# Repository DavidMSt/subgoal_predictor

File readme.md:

# subgoal predictor

Software accompanying the Master's thesis:

**Consensus through Learning: Graph Neural Networks for Task Allocation under Motion Constraints**

This repository contains the simulation and learning code developed for the thesis. It builds on the BilboLab robotics framework originally developed at the Control Systems Group, TU Berlin, and extends it with thesis-specific modules for multi-agent task assignment, motion planning, trajectory execution, and reinforcement-learning-based subgoal prediction.

The thesis investigates whether a learned coordination layer can improve multi-robot task execution in spatially constrained environments. The focus is not end-to-end learned control. Instead, the learned policy predicts intermediate subgoals and wait times, while trajectory generation remains handled by a classical motion-planning pipeline.

---

## Repository status

This repository contains research code produced for a Master's thesis. It is not a cleaned production framework.

The repository state corresponding to the thesis submission is tagged as:

```text
thesis-submission-2026-04-30
```

Use this tag, or the exact commit hash referenced in the thesis, when reproducing results.

The most relevant thesis-specific code is located in:

```text
software/master_thesis/
```

The rest of the repository contains the underlying BilboLab framework, robot infrastructure, GUI components, simulation utilities, firmware-related files, and hardware/testbed material inherited from or derived from the upstream BilboLab project.

---

## Thesis-specific contribution

The thesis-specific implementation extends BilboLab with a modular multi-agent coordination pipeline:

```text
Task Assignment → Subgoal Prediction → Motion Planning → Execution
```

The main components are:

- **Task assignment module**  
  Provides interfaces for assigning agents to tasks. Classical strategies such as the Hungarian algorithm are used for evaluation. DGNN-GA-related code is included as a compatible decentralized assignment component, but the final thesis evaluation fixes assignment with the Hungarian algorithm in order to isolate the subgoal predictor.

- **Subgoal predictor**  
  Reinforcement-learning policy trained to predict intermediate positions and wait times. The goal is to stage agents before contested passages and reduce unresolved congestion.

- **Motion-planning module**  
  OMPL/FCL-based planning pipeline for generating collision-checked paths under the robot model. Planned paths are post-processed and converted into executable trajectories.

- **Execution module**  
  Applies planned trajectories step by step in the BilboLab simulation loop and handles waiting phases, task completion, and replanning/failure states.

- **Scenario and evaluation infrastructure**  
  Contains fixed and randomized multi-agent scenarios used for training, evaluation, debugging, and visualization.

---

## Directory overview

The thesis-specific package is structured as follows:

```text
software/master_thesis/
├── containers/          # Shared state/config containers
├── general/             # Base thesis-specific simulation and agent layer
├── universal/           # Extended simulation/agent layer with TA → MP → EXE pipeline
├── modules/
│   ├── task_assignment/     # Assignment interfaces and solvers
│   ├── motion_planning/     # OMPL/FCL planning and trajectory generation
│   ├── execution/           # Trajectory execution and reactive execution logic
│   ├── subgoal_predictor/   # RL subgoal policy, training, inference, and design notes
│   └── local_control/       # Low-level/local controller experiments
├── scenarios/           # Scenario definitions and YAML files
└── gui/                 # Thesis-specific GUI entry points
```

The top-level repository also contains the broader BilboLab structure:

```text
software/       # Host-side framework and thesis code
robots/         # Robot platform code and related infrastructure
libraries/      # Shared software libraries
testbed/        # Physical testbed configuration
electronics/    # Electronics-related material
material/        # Supporting material
```

---

## Main thesis pipeline

The evaluated pipeline fixes task assignment using the Hungarian algorithm in order to isolate the learned subgoal predictor. The learned policy is then evaluated as an intermediate coordination layer between task assignment and motion planning.

The execution flow is:

1. Load a multi-agent scenario.
2. Assign each agent to one task.
3. Construct local observations for each agent.
4. Predict optional subgoals and wait times.
5. Plan motion to subgoals and final tasks.
6. Execute planned trajectories in simulation.
7. Log termination rate, makespan, planning failures, planning time, wait time, and subgoal-related metrics.

This separation is important: the policy does not replace the motion planner. It only changes the intermediate targets given to the planner.

---

## Important modules

### Task assignment

```text
software/master_thesis/modules/task_assignment/
```

Contains the task-assignment interface and available assignment strategies. The final experiments use the Hungarian algorithm as a fixed assignment solver to isolate the subgoal predictor. DGNN-GA-related code is included as a decentralized assignment option and system-level compatibility component, but the final thesis results do not evaluate the full DGNN-GA + subgoal-prediction pipeline.

### Motion planning

```text
software/master_thesis/modules/motion_planning/
```

Contains the planner interface, OMPL adapter, trajectory planner, and related planning utilities. The planner receives agent state, target state, map information, and robot geometry, then returns either a trajectory representation or a planning failure state.

### Execution

```text
software/master_thesis/modules/execution/
```

Contains the logic that applies planned trajectories during the simulation loop. This layer bridges planner output and simulated robot motion.

### Subgoal prediction

```text
software/master_thesis/modules/subgoal_predictor/
```

Contains the reinforcement-learning subgoal predictor, training code, subgoal manager, and design notes. The policy predicts intermediate target positions and wait times from local observations. These predictions are passed back into the same motion-planning and execution modules used by the non-learning baseline.

Relevant files include:

```text
rl_subgoal_predictor.py
subgoal_manager.py
train_subgoal.py
architecture_notes.md
obs_design_notes.md
reward_design_notes.md
```

### Scenarios

```text
software/master_thesis/scenarios/
```

Contains YAML and Python scenario definitions. The scenarios include fixed and randomized setups with different numbers of agents and bottleneck configurations, such as one-gap and two-gap environments.

Examples include:

```text
rl_5n_fixed_1gap_2x2.yaml
rl_8n_fixed_1gap_2x3.yaml
rl_10n_fixed_2gap_3x3.yaml
```

---

## Running the code

Most thesis code is intended to be run from the `software/` directory with the repository root available on the Python path.

Example:

```bash
cd software
PYTHONPATH=. python -m master_thesis.modules.subgoal_predictor.train_subgoal
```

For GUI-based inspection:

```bash
cd software
PYTHONPATH=. python master_thesis/gui/thesis_gui.py
```

Exact training and evaluation commands may depend on the scenario, checkpoint, and experiment configuration. The code is research-oriented and not packaged as a standalone installable library.

---

## Dependencies

The host-side Python dependencies are listed in:

```text
software/requirements.txt
```

Some dependencies may require manual installation, especially:

- **OMPL** for motion planning
- **FCL / python-fcl** for collision checking
- **PyTorch** for neural-network training
- **TensorBoard** for training logs

OMPL may need to be installed from a platform-specific wheel or from source, depending on the system.

---

## Relationship to BilboLab

This repository is forked from the original BilboLab framework. BilboLab provides the underlying simulation infrastructure, robot abstractions, GUI framework, and broader robotics software stack. The thesis code is implemented as an extension on top of that infrastructure.

The thesis-specific additions are concentrated in:

```text
software/master_thesis/
```

The core thesis experiments do not require understanding the full firmware, electronics, or physical robot stack.

---

## Reproducing thesis results

The thesis results were generated from the simulation and learning pipeline in:

```text
software/master_thesis/
```

For strict reproducibility, use the thesis submission tag:

```bash
git checkout thesis-submission-2026-04-30
```

The thesis appendix documents the software architecture at a high level. This repository contains the implementation, configuration files, scenario definitions, and training/evaluation infrastructure. The code is research-oriented and some paths or scripts may depend on the local development environment used during the thesis.

---

## Citation / attribution

If you use this repository, please cite the corresponding thesis:

```text
David Stoll.
Consensus through Learning: Graph Neural Networks for Task Allocation under Motion Constraints.
Master's thesis, Technische Universität Berlin, 2026.
```

The underlying BilboLab framework was originally developed by Dustin Lehmann at the Control Systems Group, TU Berlin.

---

## License

This repository contains research code developed in the context of a Master's thesis and builds on BilboLab. Licensing and reuse conditions should be clarified with the author and/or original BilboLab maintainers before external use.

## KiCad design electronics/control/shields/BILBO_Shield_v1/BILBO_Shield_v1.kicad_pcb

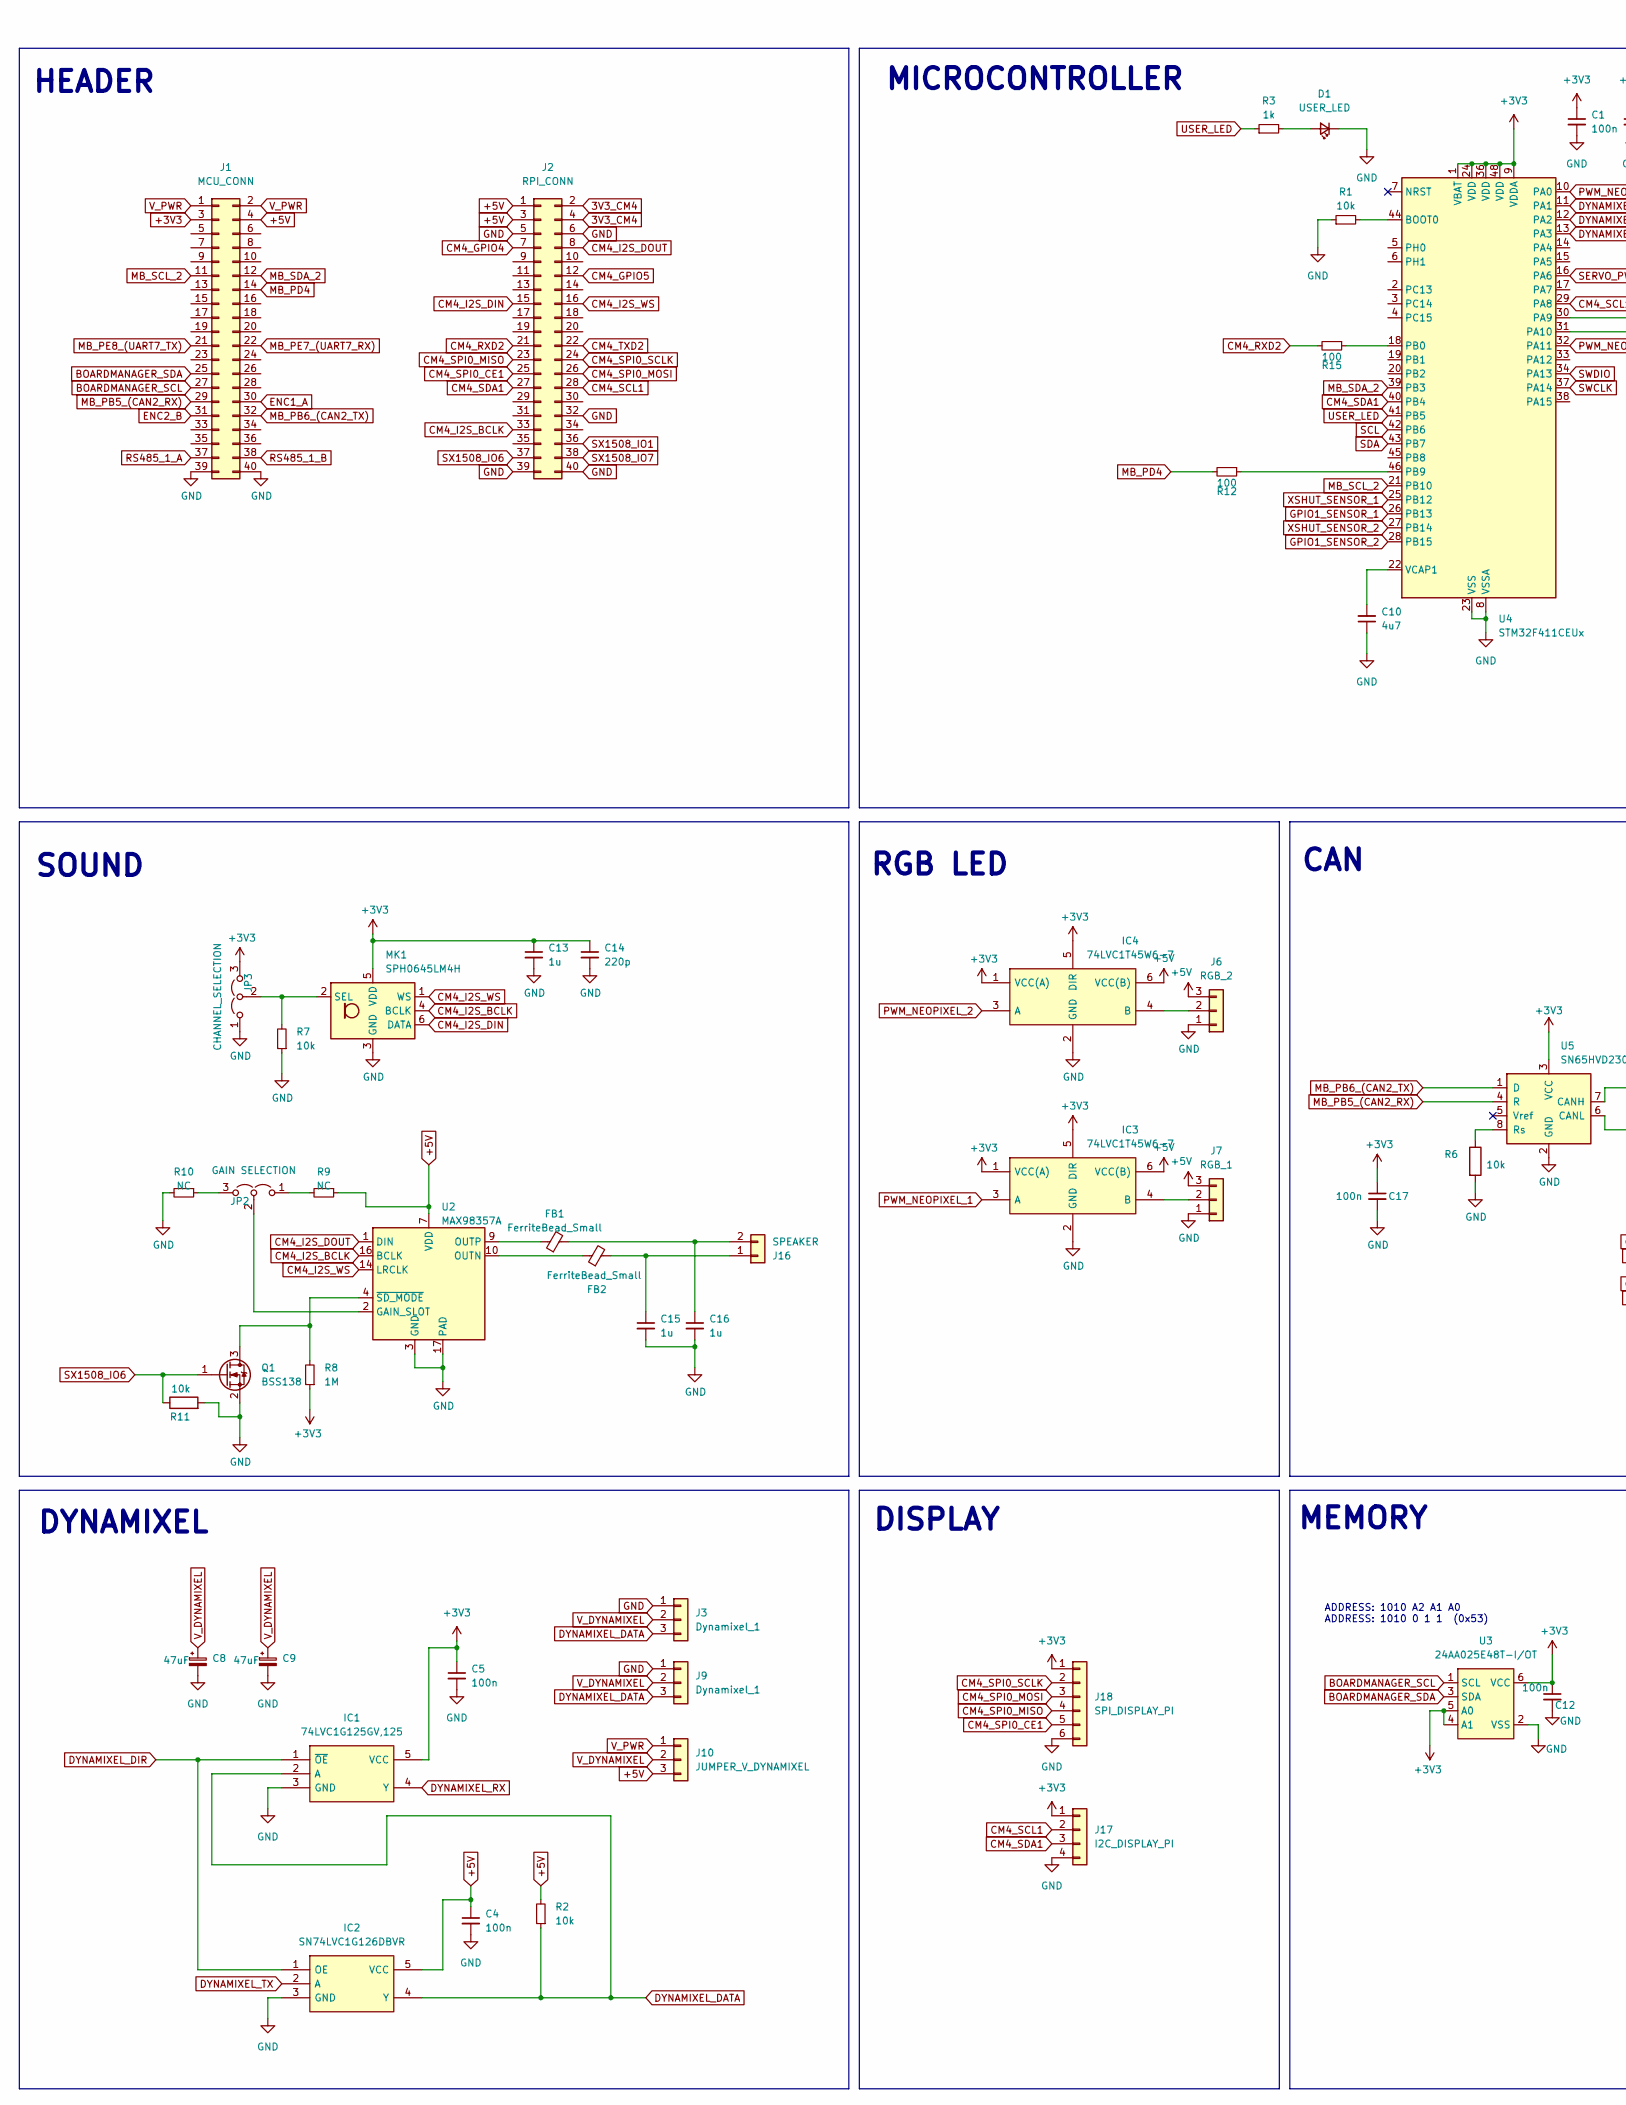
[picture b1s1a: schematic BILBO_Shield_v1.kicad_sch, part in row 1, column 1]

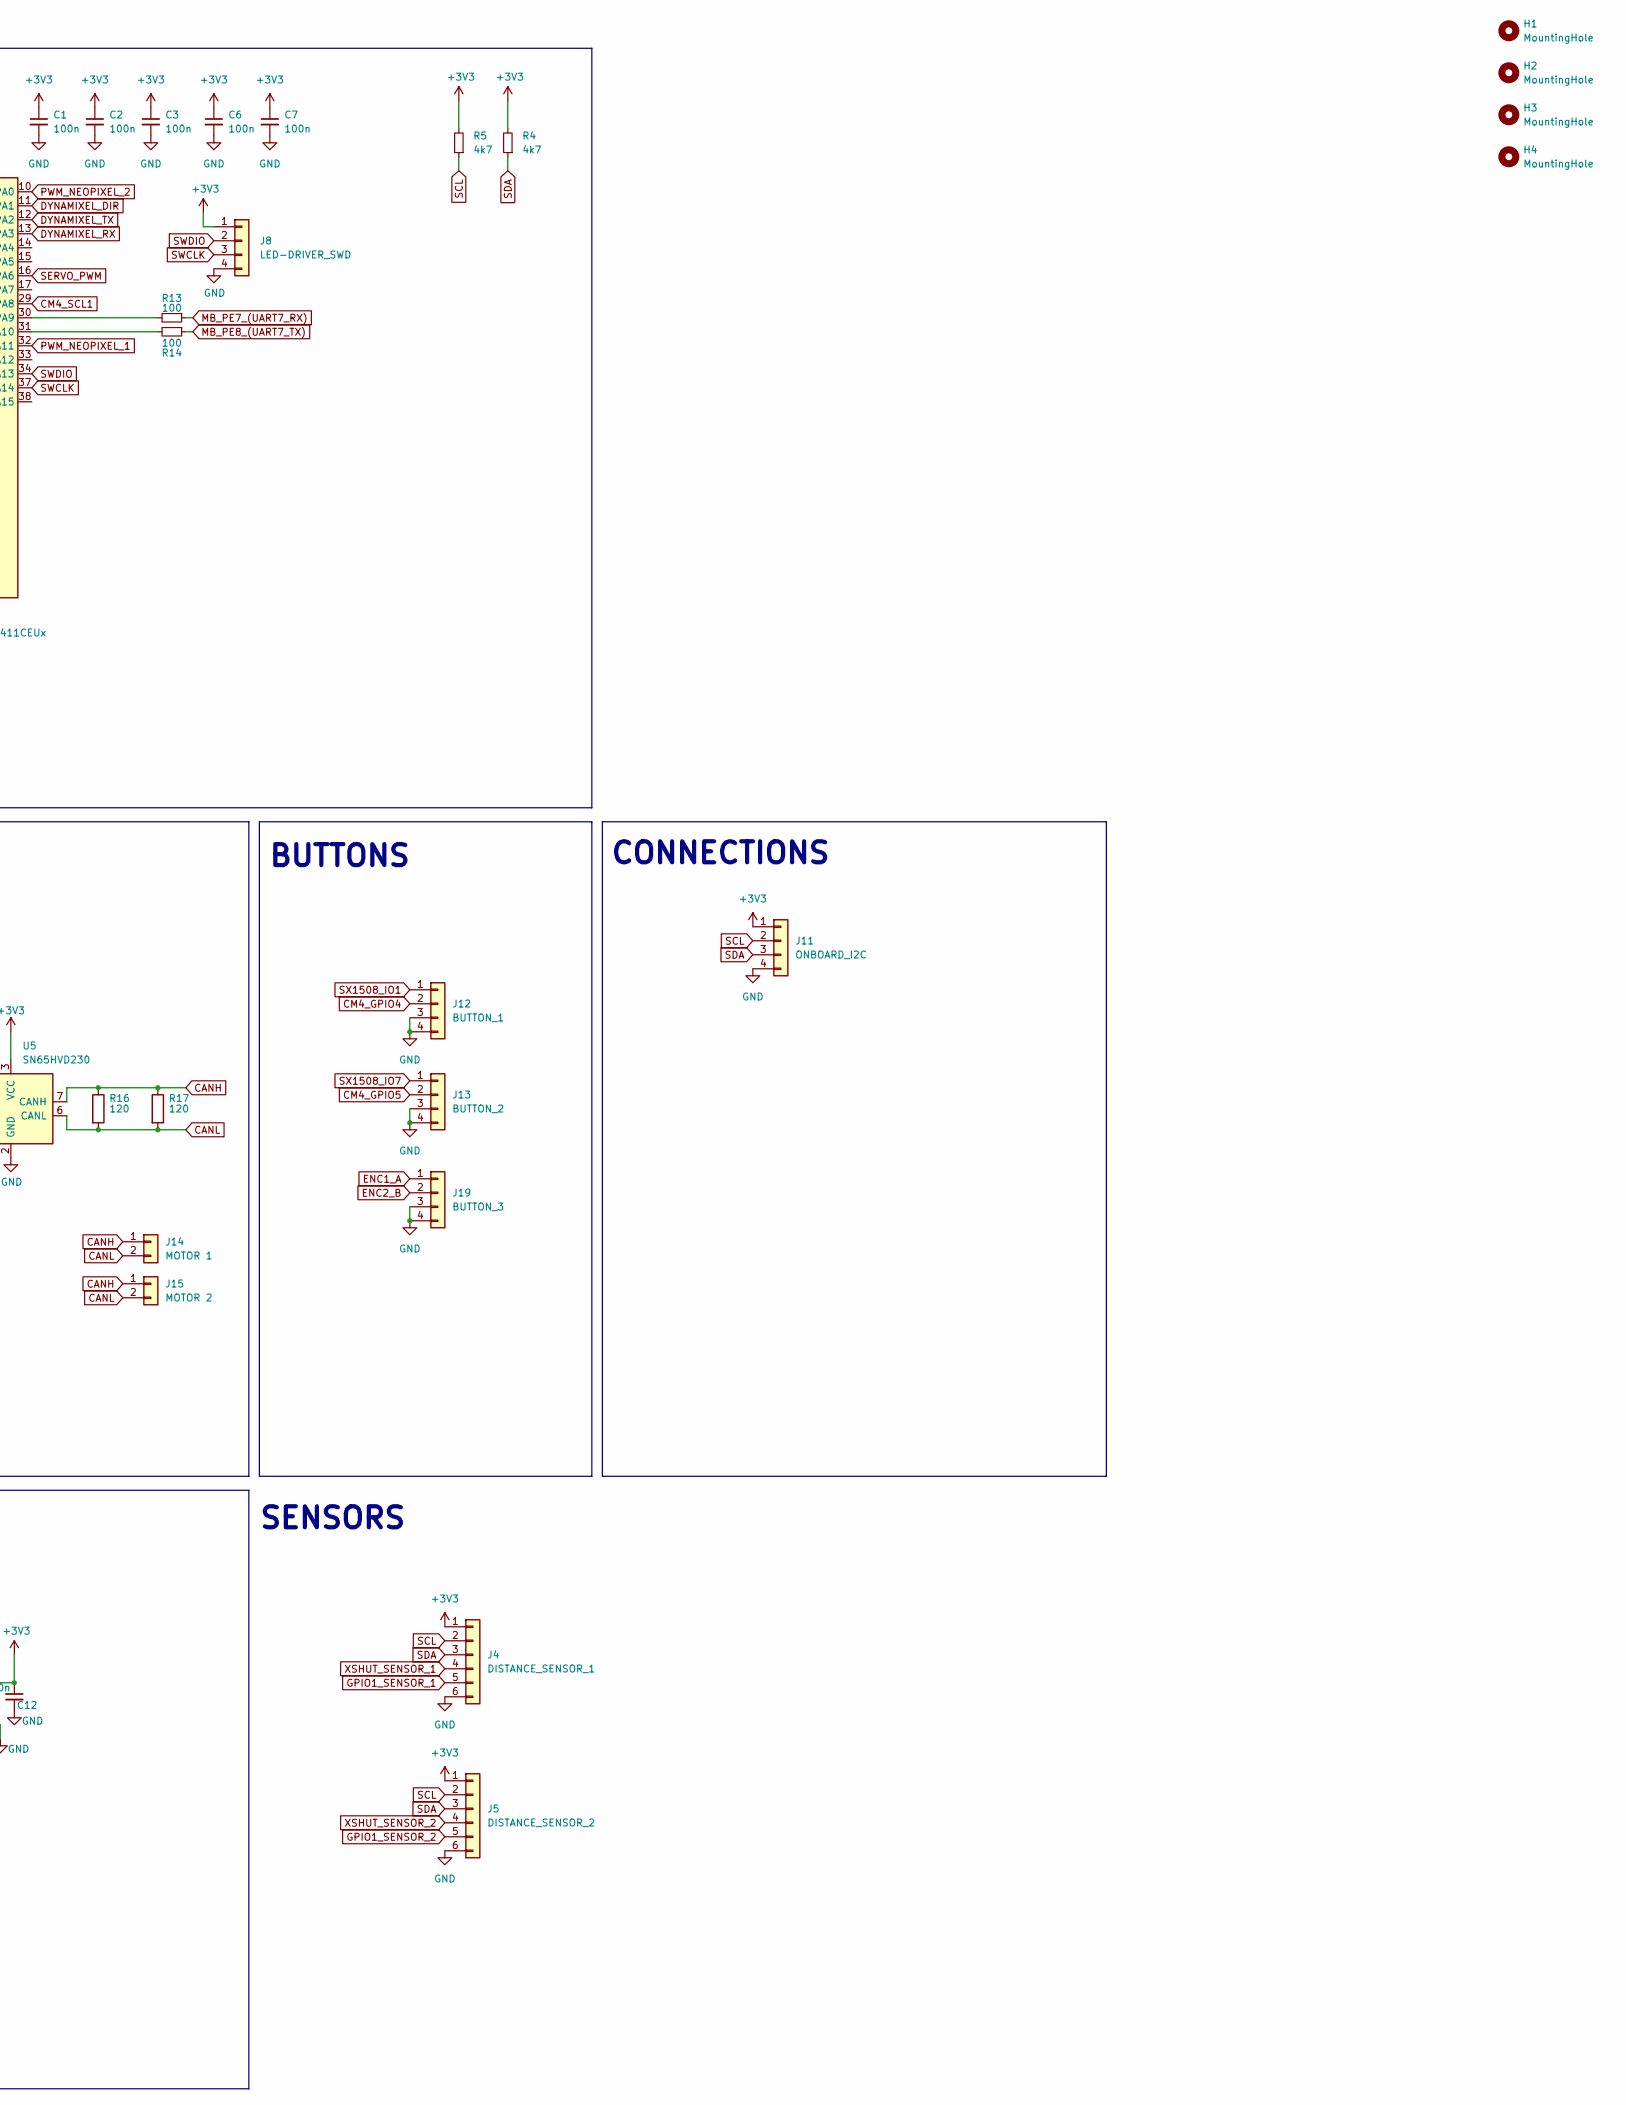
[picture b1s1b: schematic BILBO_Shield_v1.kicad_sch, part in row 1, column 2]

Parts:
C1, C2, C3, C4, C5, C6, C7, C12, C17: 100n; C_0603_1608Metric
C8, C9: 47uF; CP_Elec_6.3x5.2
C10: 4u7; C_0805_2012Metric
C13, C15, C16: 1u; C_0603_1608Metric
C14: 220p; C_0603_1608Metric
D1: USER_LED; LED_0603_1608Metric
FB1, FB2: FerriteBead_Small; C_0805_2012Metric
H1, H2, H3, H4: MountingHole; MountingHole_2.7mm_M2.5_DIN965
IC1: 74LVC1G125GV,125; SOT95P275X110-5N; Mouser Part Number 771-74LVC1G125GV
IC2: SN74LVC1G126DBVR; SOT95P280X145-5N; Mouser Part Number 595-SN74LVC1G126DBVR
IC3, IC4: 74LVC1T45W6-7; SOT95P285X140-6N; Mouser Part Number 621-74LVC1T45W6-7
J1: MCU_CONN; PinHeader_2x20_P2.54mm_Vertical
J2: RPI_CONN; PinHeader_2x20_P2.54mm_Vertical
J3, J9: Dynamixel_1; JST_XH_B3B-XH-A_1x03_P2.50mm_Vertical
J4: DISTANCE_SENSOR_1; JST_GH_BM06B-GHS-TBT_1x06-1MP_P1.25mm_Vertical
J5: DISTANCE_SENSOR_2; JST_GH_BM06B-GHS-TBT_1x06-1MP_P1.25mm_Vertical
J6: RGB_2; JST_GH_BM03B-GHS-TBT_1x03-1MP_P1.25mm_Vertical
J7: RGB_1; JST_GH_BM03B-GHS-TBT_1x03-1MP_P1.25mm_Vertical
J8: LED-DRIVER_SWD; JST_SH_SM04B-SRSS-TB_1x04-1MP_P1.00mm_Horizontal
J10: JUMPER_V_DYNAMIXEL; PinHeader_1x03_P2.54mm_Vertical
J11: ONBOARD_I2C; JST_GH_BM04B-GHS-TBT_1x04-1MP_P1.25mm_Vertical
J12: BUTTON_1; JST_GH_BM04B-GHS-TBT_1x04-1MP_P1.25mm_Vertical
J13: BUTTON_2; JST_GH_BM04B-GHS-TBT_1x04-1MP_P1.25mm_Vertical
J14: MOTOR 1; JST_GH_BM02B-GHS-TBT_1x02-1MP_P1.25mm_Vertical
J15: MOTOR 2; JST_GH_BM02B-GHS-TBT_1x02-1MP_P1.25mm_Vertical
J16: SPEAKER; JST_PH_B2B-PH-K_1x02_P2.00mm_Vertical
J17: I2C_DISPLAY_PI; JST_GH_BM04B-GHS-TBT_1x04-1MP_P1.25mm_Vertical
J18: SPI_DISPLAY_PI; JST_GH_BM06B-GHS-TBT_1x06-1MP_P1.25mm_Vertical
J19: BUTTON_3; JST_GH_BM04B-GHS-TBT_1x04-1MP_P1.25mm_Vertical
JP2: GAIN SELECTION; SolderJumper-3_P1.3mm_Open_Pad1.0x1.5mm
JP3: CHANNEL_SELECTION; SolderJumper-3_P1.3mm_Open_Pad1.0x1.5mm
MK1: SPH0645LM4H; Knowles_SPH0645LM4H-6_3.5x2.65mm
Q1: BSS138; SOT-23
R1, R2, R7: 10k; R_0603_1608Metric
R3: 1k; R_0603_1608Metric
R4, R5: 4k7; R_0603_1608Metric
R6: 10k; R_0603_1608Metric; Part Description Resistor 2.2K M1005 1% 63mW
R8: 1M; R_0603_1608Metric
R9, R10: NC; R_0603_1608Metric
R11: 10k; R_0603_1608Metric; Part Description Resistor 1K M1005 1% 63mW
R12, R13, R14, R15: 100; R_0603_1608Metric
R16, R17: 120; R_0603_1608Metric; Part Description Resistor 2.2K M1005 1% 63mW
U2: MAX98357A; TQFN-16-1EP_3x3mm_P0.5mm_EP1.23x1.23mm
U3: 24AA025E48T-I/OT; SOT-23-6_Handsoldering
U4: STM32F411CEUx; QFN-48-1EP_7x7mm_P0.5mm_EP5.6x5.6mm
U5: SN65HVD230; SOIC127P600X175-8N

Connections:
3V3_CM4: J2.2, J2.4
+3V3: C1.1, C2.1, C3.1, C5.1, C6.1, C7.1, C12.1, C13.1, C14.1, C17.1, IC1.5 (VCC), IC3.1 (VCC(A)), IC3.5 (DIR), IC4.1 (VCC(A)), IC4.5 (DIR), J1.3, J4.1, J5.1, J8.1, J11.1, J17.1, J18.1, JP3.3 (B), MK1.5 (VDD), R4.2, R5.2, R8.1, U3.4 (A1), U3.5 (A0), U3.6 (VCC), U4.1 (VBAT), U4.9 (VDDA), U4.24 (VDD), U4.36 (VDD), U4.48 (VDD), U5.3 (VCC)
+5V: C4.1, IC2.5 (VCC), IC3.6 (VCC(B)), IC4.6 (VCC(B)), J1.4, J2.1, J2.3, J6.3, J7.3, J10.3, R2.2, R9.1, U2.7 (VDD), U2.8 (VDD)
BOARDMANAGER_SCL: J1.27, U3.1 (SCL)
BOARDMANAGER_SDA: J1.25, U3.3 (SDA)
CANH: J14.1, J15.1, R16.1, R17.1, U5.7 (CANH)
CANL: J14.2, J15.2, R16.2, R17.2, U5.6 (CANL)
CM4_GPIO4: J2.7, J12.2
CM4_GPIO5: J2.12, J13.2
CM4_I2S_BCLK: J2.33, MK1.4 (BCLK), U2.16 (BCLK)
CM4_I2S_DIN: J2.15, MK1.6 (DATA)
CM4_I2S_DOUT: J2.8, U2.1 (DIN)
CM4_I2S_WS: J2.16, MK1.1 (WS), U2.14 (LRCLK)
CM4_RXD2: J2.21, R15.2
CM4_SCL1: J2.28, J17.2, U4.29 (PA8)
CM4_SDA1: J2.27, J17.3, U4.40 (PB4)
CM4_SPI0_CE1: J2.25, J18.5
CM4_SPI0_MISO: J2.23, J18.4
CM4_SPI0_MOSI: J2.26, J18.3
CM4_SPI0_SCLK: J2.24, J18.2
CM4_TXD2: J2.22
DYNAMIXEL_DATA: IC1.2 (A), IC2.4 (Y), J3.3, J9.3, R2.1
DYNAMIXEL_DIR: IC1.1 (~OE), IC2.1 (OE), U4.11 (PA1)
DYNAMIXEL_RX: IC1.4 (Y), U4.13 (PA3)
DYNAMIXEL_TX: IC2.2 (A), U4.12 (PA2)
ENC1_A: J1.30, J19.1
ENC2_B: J1.31, J19.2
GND: C1.2, C2.2, C3.2, C4.2, C5.2, C6.2, C7.2, C8.2, C9.2, C10.1, C12.2, C13.2, C14.2, C15.2, C16.2, C17.2, D1.1 (K), IC1.3 (GND), IC2.3 (GND), IC3.2 (GND), IC4.2 (GND), J1.39, J1.40, J2.5, J2.6, J2.32, J2.39, J2.40, J3.1, J4.6, J5.6, J6.1, J7.1, J8.4, J9.1, J11.4, J12.3, J12.4, J13.3, J13.4, J17.4, J18.6, J19.3, J19.4, JP3.1 (A), MK1.3 (GND), Q1.2 (S), R1.1, R6.2, R7.1, R10.2, R11.2, U2.3 (GND), U2.11 (GND), U2.15 (GND), U2.17 (PAD), U3.2 (VSS), U4.8 (VSSA), U4.23 (VSS), U4.35 (VSS), U4.47 (VSS), U4.49 (VSS), U5.2 (GND)
GPIO1_SENSOR_1: J4.5, U4.26 (PB13)
GPIO1_SENSOR_2: J5.5, U4.28 (PB15)
MB_PB5_(CAN2_RX): J1.29, U5.4 (R)
MB_PB6_(CAN2_TX): J1.32, U5.1 (D)
MB_PD4: J1.14, R12.2
MB_PE7_(UART7_RX): J1.22, R13.1
MB_PE8_(UART7_TX): J1.21, R14.1
MB_SCL_2: J1.11, U4.21 (PB10)
MB_SDA_2: J1.12, U4.39 (PB3)
unnamed: D1.2 (A), R3.2
unnamed: IC3.4 (B), J7.2
unnamed: IC4.4 (B), J6.2
unnamed: C15.1, FB2.2, J16.1
unnamed: C16.1, FB1.2, J16.2
unnamed: JP2.1 (A), R9.2
unnamed: JP2.3 (B), R10.1
unnamed: JP2.2 (C), U2.2 (GAIN_SLOT)
unnamed: JP3.2 (C), MK1.2 (SEL), R7.2
unnamed: Q1.3 (D), R8.2, U2.4 (~SD_MODE)
unnamed: FB2.1, U2.10 (OUTN)
unnamed: FB1.1, U2.9 (OUTP)
unnamed: R1.2, U4.44 (BOOT0)
unnamed: R13.2, U4.30 (PA9)
unnamed: R14.2, U4.31 (PA10)
unnamed: R15.1, U4.18 (PB0)
unnamed: R12.1, U4.46 (PB9)
unnamed: C10.2, U4.22 (VCAP1)
unnamed: R6.1, U5.8 (Rs)
PWM_NEOPIXEL_1: IC3.3 (A), U4.32 (PA11)
PWM_NEOPIXEL_2: IC4.3 (A), U4.10 (PA0)
RS485_1_A: J1.37
RS485_1_B: J1.38
SCL: J4.2, J5.2, J11.2, R5.1, U4.42 (PB6)
SDA: J4.3, J5.3, J11.3, R4.1, U4.43 (PB7)
SERVO_PWM: U4.16 (PA6)
SWCLK: J8.3, U4.37 (PA14)
SWDIO: J8.2, U4.34 (PA13)
SX1508_IO1: J2.36, J12.1
SX1508_IO6: J2.37, Q1.1 (G), R11.1
SX1508_IO7: J2.38, J13.1
USER_LED: R3.1, U4.41 (PB5)
V_DYNAMIXEL: C8.1, C9.1, J3.2, J9.2, J10.2
V_PWR: J1.1, J1.2, J10.1
XSHUT_SENSOR_1: J4.4, U4.25 (PB12)
XSHUT_SENSOR_2: J5.4, U4.27 (PB14)

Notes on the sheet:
SENSORS
SOUND
MICROCONTROLLER
ADDRESS: 1010 A2 A1 A0 ADDRESS: 1010 0 1 1 (0x53)
DISPLAY
MEMORY
CONNECTIONS
HEADER
DYNAMIXEL
RGB LED
BUTTONS
CAN

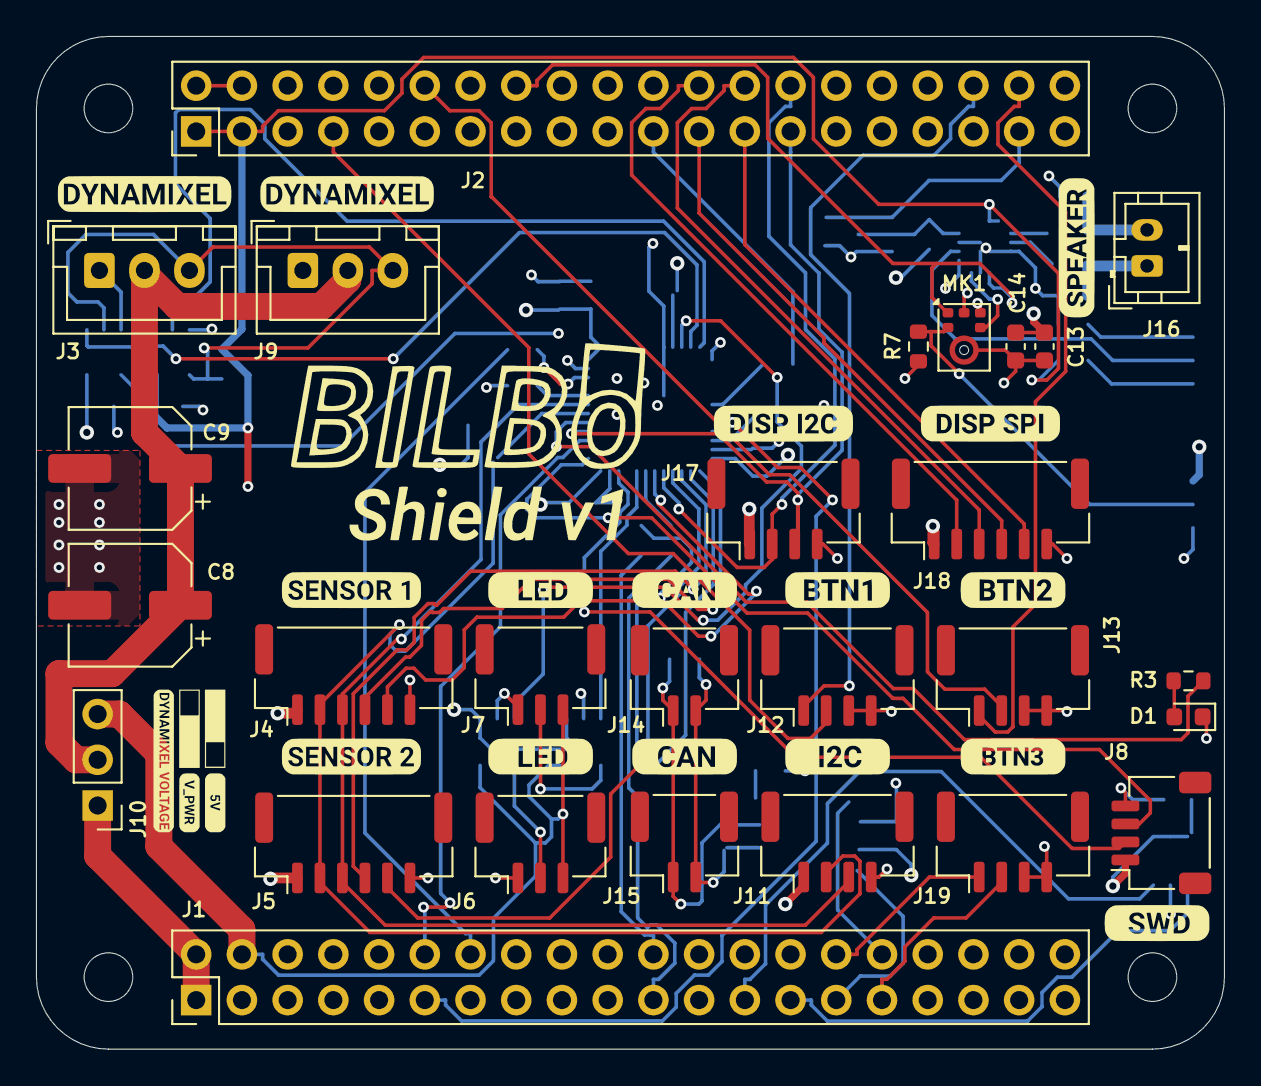
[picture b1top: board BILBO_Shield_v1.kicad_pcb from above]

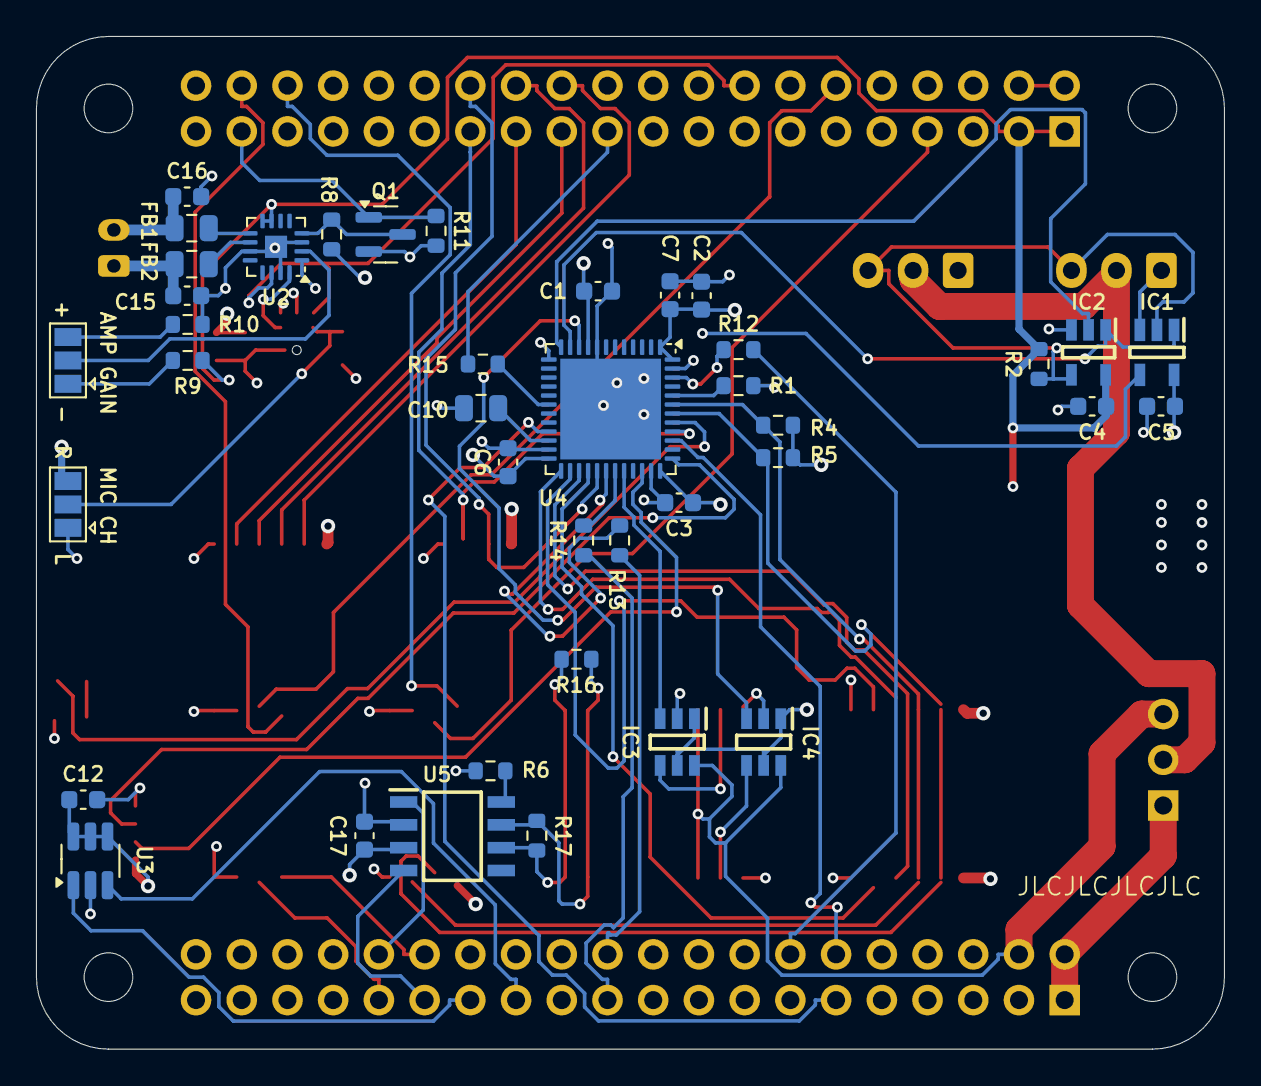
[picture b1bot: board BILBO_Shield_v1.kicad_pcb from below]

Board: 4 copper layers, 66.0 x 56.3 mm, 71 parts (40 on the bottom side), 69 nets.
